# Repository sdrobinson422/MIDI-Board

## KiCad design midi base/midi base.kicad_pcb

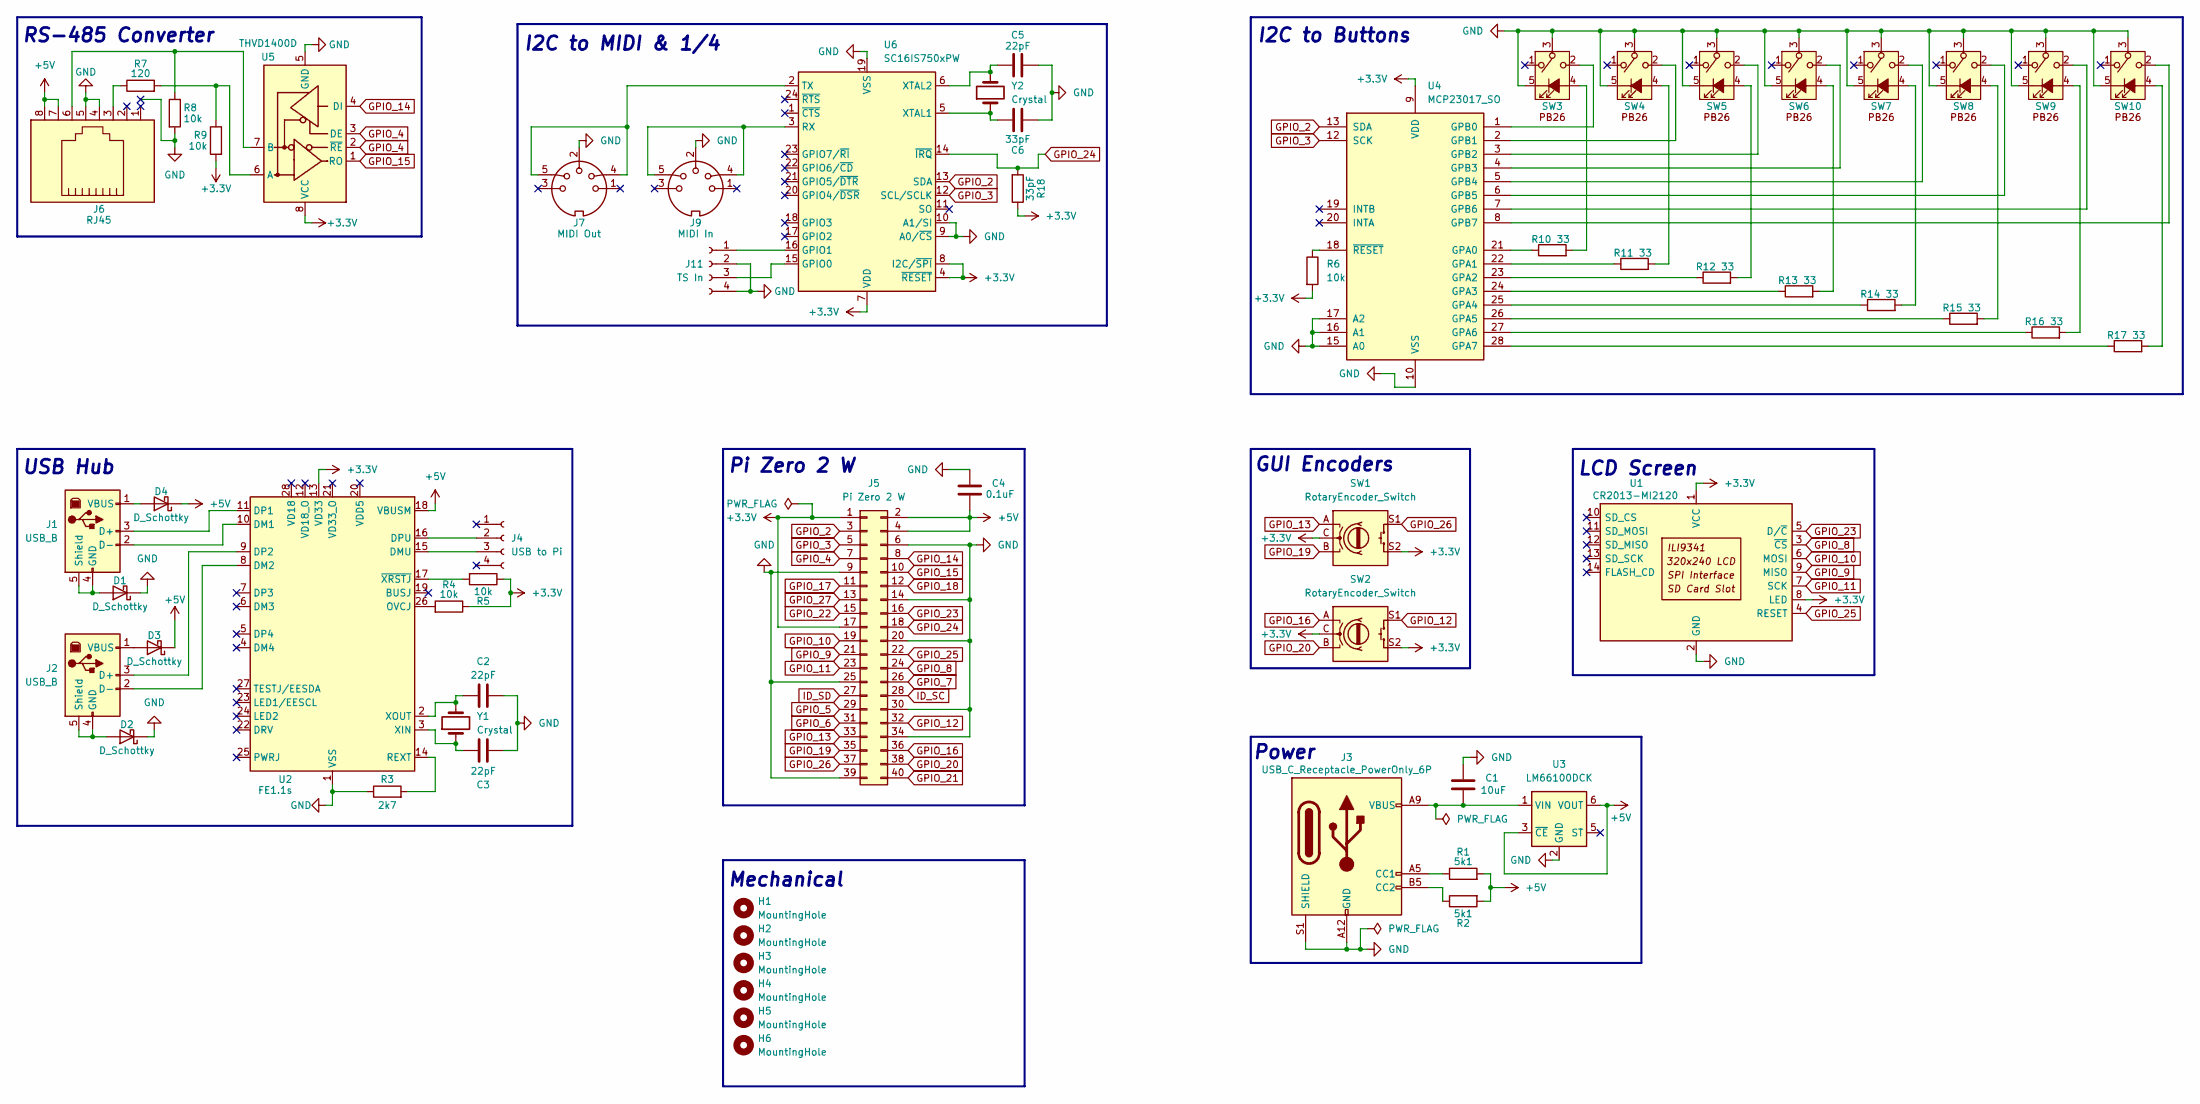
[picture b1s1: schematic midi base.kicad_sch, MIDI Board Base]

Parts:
C1: 10uF; C_0603_1608Metric
C2, C3, C5: 22pF; C_0402_1005Metric
C4: 0.1uF; C_0603_1608Metric
C6: 33pF; C_0402_1005Metric
D1, D2, D3, D4: D_Schottky; D_0603_1608Metric
H1, H2, H3, H4, H5, H6: MountingHole; MountingHole_3.2mm_M3
J1: USB_B; USB_B_OST_USB-B1HSxx_Horizontal
J2: USB_B; USB_B_Lumberg_2411_02_Horizontal
J3: USB_C_Receptacle_PowerOnly_6P; USB_C_Receptacle_GCT_USB4135-GF-A_6P_TopMnt_Horizontal
J4: USB to Pi; JST_XH_B4B-XH-A_1x04_P2.50mm_Vertical
J5: Pi Zero 2 W; PinHeader_2x20_P2.54mm_Vertical
J6: RJ45; RJ45_Amphenol_RJHSE5380
J7: MIDI Out; JST_XH_B5B-XH-A_1x05_P2.50mm_Vertical
J9: MIDI In; JST_XH_B5B-XH-A_1x05_P2.50mm_Vertical
J11: TS In; JST_XH_B4B-XH-A_1x04_P2.50mm_Vertical
R1, R2: 5k1; R_0603_1608Metric
R3: 2k7; R_0402_1005Metric
R4, R5, R6, R8, R9: 10k; R_0402_1005Metric
R7: 120; R_0603_1608Metric
R10, R11, R12, R13, R14, R15, R16, R17: 33; R_0402_1005Metric
R18: 33pF; R_0402_1005Metric
SW1, SW2: RotaryEncoder_Switch; RotaryEncoder_Alps_EC11E-Switch_Vertical_H20mm
SW3, SW4, SW5, SW6, SW7, SW8, SW9, SW10: Honyone_PB26
U1: CR2013-MI2120
U2: FE1.1s; SSOP-28_3.9x9.9mm_P0.635mm
U3: LM66100DCK; SOT-363_SC-70-6
U4: MCP23017_SO; SOIC-28W_7.5x17.9mm_P1.27mm
U5: THVD1400D; SOIC-8_3.9x4.9mm_P1.27mm
U6: SC16IS750xPW; TSSOP-24_4.4x7.8mm_P0.65mm
Y1, Y2: Crystal; Crystal_SMD_2012-2Pin_2.0x1.2mm

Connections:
+3.3V: J5.1, J5.17, R4.1, R5.1, R6.2, R9.2, R18.1, SW1.C, SW1.S2, SW2.C, SW2.S2, U1.1 (VCC), U1.8 (LED), U2.13 (VD33), U4.9 (VDD), U5.8 (VCC), U6.4 (~RESET), U6.7 (VDD), U6.8 (I2C/~SPI)
+5V: C4.1, D3.1 (K), D4.1 (K), J5.2, J5.4, J6.7, J6.8, R1.2, R2.2, U2.18 (VBUSM), U3.3 (~CE), U3.6 (VOUT)
GND: C1.2, C2.2, C3.2, C4.2, C5.2, C6.2, D1.1 (K), D2.1 (K), J3.A12 (GND), J3.B12 (GND), J3.S1 (SHIELD), J5.6, J5.9, J5.14, J5.20, J5.25, J5.30, J5.34, J5.39, J6.4, J6.5, J7.2, J9.2, J11.2, J11.4, R3.1, R8.2, SW3.3, SW3.5, SW4.3, SW4.5, SW5.3, SW5.5, SW6.3, SW6.5, SW7.3, SW7.5, SW8.3, SW8.5, SW9.3, SW9.5, SW10.3, SW10.5, U1.2 (GND), U2.1 (VSS), U3.2 (GND), U4.10 (VSS), U4.15 (A0), U4.16 (A1), U4.17 (A2), U5.5 (GND), U6.9 (A0/~CS), U6.10 (A1/SI), U6.19 (VSS)
GPIO_2: J5.3, U4.13 (SDA), U6.13 (SDA)
GPIO_3: J5.5, U4.12 (SCK), U6.12 (SCL/SCLK)
GPIO_4: J5.7, U5.2 (~RE), U5.3 (DE)
GPIO_5: J5.29
GPIO_6: J5.31
GPIO_7: J5.26
GPIO_8: J5.24, U1.3 (~CS)
GPIO_9: J5.21, U1.9 (MISO)
GPIO_10: J5.19, U1.6 (MOSI)
GPIO_11: J5.23, U1.7 (SCK)
GPIO_12: J5.32, SW2.S1
GPIO_13: J5.33, SW1.A
GPIO_14: J5.8, U5.4 (DI)
GPIO_15: J5.10, U5.1 (RO)
GPIO_16: J5.36, SW2.A
GPIO_17: J5.11
GPIO_18: J5.12
GPIO_19: J5.35, SW1.B
GPIO_20: J5.38, SW2.B
GPIO_21: J5.40
GPIO_22: J5.15
GPIO_23: J5.16, U1.5 (D/~C)
GPIO_24: J5.18, R18.2, U6.14 (~IRQ)
GPIO_25: J5.22, U1.4 (RESET)
GPIO_26: J5.37, SW1.S1
GPIO_27: J5.13
ID_SC: J5.28
ID_SD: J5.27
unnamed: D1.2 (A), J1.4 (GND), J1.5 (Shield)
unnamed: D2.2 (A), J2.4 (GND), J2.5 (Shield)
unnamed: D3.2 (A), J2.1 (VBUS)
unnamed: D4.2 (A), J1.1 (VBUS)
unnamed: J1.3 (D+), U2.11 (DP1)
unnamed: J1.2 (D-), U2.10 (DM1)
unnamed: J2.3 (D+), U2.9 (DP2)
unnamed: J2.2 (D-), U2.8 (DM2)
unnamed: J3.A5 (CC1), R1.1
unnamed: J3.B5 (CC2), R2.1
unnamed: J4.2, U2.16 (DPU)
unnamed: J4.3, U2.15 (DMU)
unnamed: J6.3, R7.1
unnamed: J11.1, U6.16 (GPIO1)
unnamed: J11.3, U6.15 (GPIO0)
unnamed: R10.2, SW3.4
unnamed: R11.2, SW4.4
unnamed: R12.2, SW5.4
unnamed: R13.2, SW6.4
unnamed: R14.2, SW7.4
unnamed: R15.2, SW8.4
unnamed: R16.2, SW9.4
unnamed: R17.2, SW10.4
unnamed: R4.2, U2.26 (OVCJ)
unnamed: R3.2, U2.14 (REXT)
unnamed: C3.1, U2.3 (XIN), Y1.1
unnamed: C2.1, U2.2 (XOUT), Y1.2
unnamed: R5.2, U2.17 (~XRSTJ)
unnamed: C1.1, J3.A9 (VBUS), J3.B9 (VBUS), U3.1 (VIN)
unnamed: R10.1, U4.21 (GPA0)
unnamed: R11.1, U4.22 (GPA1)
unnamed: R12.1, U4.23 (GPA2)
unnamed: R13.1, U4.24 (GPA3)
unnamed: R14.1, U4.25 (GPA4)
unnamed: R15.1, U4.26 (GPA5)
unnamed: R16.1, U4.27 (GPA6)
unnamed: R17.1, U4.28 (GPA7)
unnamed: SW3.2, U4.1 (GPB0)
unnamed: SW4.2, U4.2 (GPB1)
unnamed: SW5.2, U4.3 (GPB2)
unnamed: SW6.2, U4.4 (GPB3)
unnamed: SW7.2, U4.5 (GPB4)
unnamed: SW8.2, U4.6 (GPB5)
unnamed: SW9.2, U4.7 (GPB6)
unnamed: SW10.2, U4.8 (GPB7)
unnamed: R6.1, U4.18 (~RESET)
unnamed: R7.2, R9.1, U5.6 (A)
unnamed: J6.6, R8.1, U5.7 (B)
unnamed: J9.4, J9.5, U6.3 (RX)
unnamed: J7.4, J7.5, U6.2 (TX)
unnamed: C6.1, U6.5 (XTAL1), Y2.1
unnamed: C5.1, U6.6 (XTAL2), Y2.2

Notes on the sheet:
I2C to Buttons
Mechanical
Power
LCD Screen
Pi Zero 2 W
RS-485 Converter
I2C to MIDI & 1/4
USB Hub
GUI Encoders

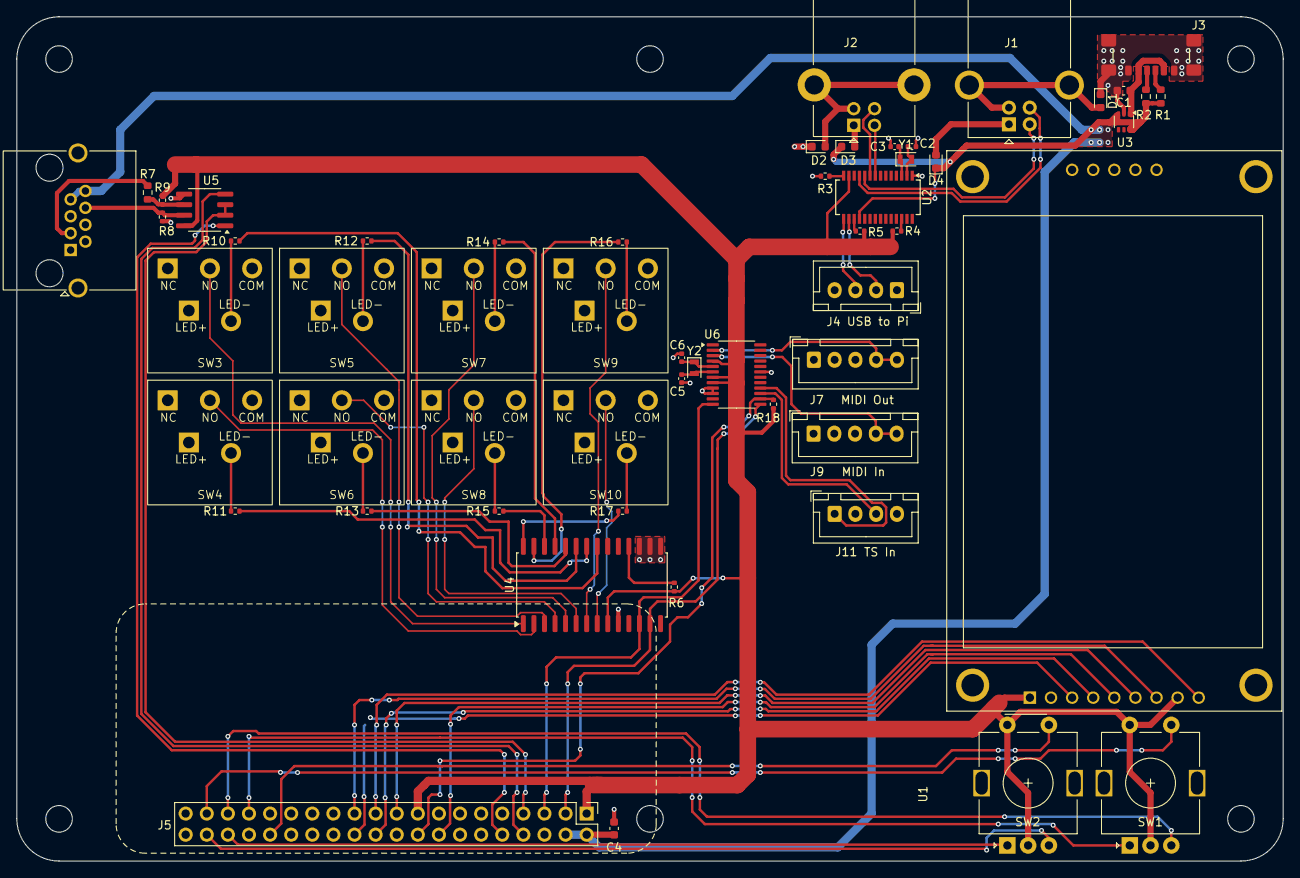
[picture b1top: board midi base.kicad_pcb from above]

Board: 2 copper layers, 152.4 x 101.6 mm, 61 parts (0 on the bottom side), 73 nets.

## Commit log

2026-06-26 fixed it
2026-06-26 added models
2026-06-26 did some stuff
2026-06-27 started pcb layout
2026-06-27 more pcb updaytes
2026-06-28 more pcb stuff
2026-06-28 even more pcb things
2026-06-28 did some funky file stuff
2026-06-28 started button expansion
